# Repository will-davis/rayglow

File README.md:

# RayGLow

Audio-reactive GLSL visuals on a custom RGB LED wall. Music plays on a desktop; a small
daemon there reduces it to per-frame audio *features* and unicasts them over UDP to a
Raspberry Pi 5, which renders Shadertoy-dialect GLSL on its GPU, packs each frame, and
ships it over a **4-lane parallel bus** to an **RP2350b** microcontroller whose PIO+DMA
engine drives the HUB75 panels with zero-CPU, jitter-free timing. Write a shader, paste
it in, watch it move to the music.

https://github.com/user-attachments/assets/fb1bfaf4-e451-43c7-8cc3-830d7c186d91

```
desktop (optional)                 Raspberry Pi 5                         RP2350b PiZero + HAT
┌────────────────────────┐         ┌────────────────────────────┐         ┌───────────────────────┐
│ music ▶ sink monitor   │  UDP    │ feed.receiver (latest-win) │  4-lane │ phase6: PIO+DMA RX    │
│ sender.py: FFT ▶ bands │ ──────▶ │ render: GLSL ▶ pack        │   bus   │ zero-CPU scan-out     │
│ + flywheels/beat/key   │  :5005  │ (to_chains ▶ hub75.pack)   │ ──────▶ │ ▶ HUB75 ▶ 384×128 wall│
│ ▶ 2996-B v3 @ ~60 Hz   │ ~180KB/s│ headless EGL + GLES3       │ 192 KB  │ (2 chains × 12 panels)│
└────────────────────────┘         └────────────────────────────┘         └───────────────────────┘
        point $RAYGLOW_HOST ──────────────▶ your Pi
```

The three stages live in **one repo**. The desktop and Pi halves are Python: the desktop
runs `sender/`, the Pi runs the `rayglow` package installed editable (`pip install -e`)
from a copy of this repo — get it there however you like (`git pull`, or a continuous
file sync such as mutagen/sshfs for live shader editing). The RP2350b half is Rust
firmware (`firmware/`) flashed onto the board, plus a custom level-shifting HAT
(`hardware/`).
First-time setup is in [Deploy](#deploy); full credits and licensing are in
[ATTRIBUTION.md](ATTRIBUTION.md) (RayGLow is **MIT** — see [LICENSE](LICENSE)).

The desktop sender is **optional**: `rayglow.fake_sender` synthesizes the same packet
struct, so the Pi can drive the wall with no music source at all.

## Why features, not streamed audio

Streaming PCM means reconstructing a continuous signal on the far end: ring buffers,
clock-drift resampling, jitter buffers. Features are **stateless per frame** — a lost or
late packet just means the Pi renders with the previous values, and at 60 Hz one held
frame is invisible. The Pi does zero audio work, the wire carries ~0.25 MB/s, and UDP
gets used the way UDP wants to be used.

## Why offload scan-out to the RP2350b

Bit-banging HUB75 from a Linux SoC fights the scheduler — it needs a dedicated RT core
and still jitters (the Pi 5's RP1 southbridge made it worse). The RP2350b runs the refresh
loop entirely in **3 PIO state machines + 4 self-chaining DMA channels**, with the CPU
never touching the pixel path. The Pi renders at whatever rate it likes and ships 192 KB
frames over the link — already gamma-corrected on the Pi (the GPU resolve pass bakes
the firmware `lut.rs` CIE curve into each frame; `--readback legacy` instead applies
the packer's bit-exact LUT replica to a LINEAR readback); the RP2350b holds a
rock-steady, flicker-free refresh.

## Why a parallel bus, not SPI

The link was originally 1-lane SPI, and SPI still works as the proven fallback
(`--transport spi`). But a frame takes ~13 ms at 40 MHz SPI even at the v1 wall's 64 KB —
~39 ms at the v2 wall's 192 KB — long enough to sit squarely
on the critical path. A **4-lane source-synchronous parallel bus**, clocked out by the
Pi 5's RP1 PIO block, drops that to ~2 ms (clkdiv 3; ~1.3 ms at clkdiv 2). Only the wire
changes: the byte stream is identical to the SPI path (same `hub75.py` packer output,
same READY handshake), so the firmware and packer don't change. (4 lanes, not 8: the RP2350b scan-out engine owns
GP0–18, leaving GP19–27 for the link.) See
[`rayglow/render/piobridge/README.md`](rayglow/render/piobridge/README.md).

## Hardware

A **Waveshare RP2350-PiZero** on a custom HAT that level-shifts (3.3 V → 5 V via
`SN74AHCT245`) and breaks out two HUB75 chains + the Pi↔RP2350b link. Design files, the
KiCad project, and fab Gerbers are in [`hardware/`](hardware/).

## Repo layout

| path | what |
|---|---|
| `sender/` | **desktop half** — the feature daemon (`sender.py`), its own uv project (numpy + sounddevice). [sender/README.md](sender/README.md) has the protocol + feature detail. |
| `rayglow/feed/` | the audio-feature feed: packet `receiver`, `FeatureState`, and the rig `config` (geometry/network/gamma). Shared, dependency-free. |
| `rayglow/render/` | **the live renderer** — headless EGL + GLES3, multipass pipeline, iChannel textures (`audio`, `milk`, noise, images), hot reload, a TCP **control plane** (`control.py`: push/switch shaders + media controls), the GPU resolve pass + zero-copy dma-heap readback (`output.py`, `dmabuf.py`), the frame packer (`hub75.py`) + link backends (`spi_out.py`, `pio_out.py` / `piobridge/`), and `presets/*.glsl`. |
| `rayglow/fake_sender.py` | music-free test harness; emits the same packet struct with synthesized features. |
| `rayglow/link.py` | **remote render wire contract** — frame fragments out, flip credits back (UDP, latest-wins, credit-paced; see [REMOTE-RENDER-PLAN.md](REMOTE-RENDER-PLAN.md)). Shared by `render/net_out.py` (`--output net`) and `framesink`. |
| `rayglow/framesink.py` | the Pi when rendering happens elsewhere: reassemble frames → `drm_out` page flip → credit per vblank. A socket and a memcpy — no GL stack. |
| `rayglow.example.toml` | per-machine CLI defaults (`rayglow/userconf.py`): pin each machine's flags (`output`, `net-host`, `window`, …) in `~/.config/rayglow/config.toml` so production launches are just `python -m rayglow.render <shader>` / `python -m rayglow.framesink`. CLI flags always override. |
| `rayglow/spi_test.py` | static test pattern (no GL) — isolates the link/firmware/cabling from the renderer. Per-panel ID markers confirm the serpentine fold; runs over either transport. |
| `firmware/` | **RP2350b Rust firmware** — zero-CPU PIO+DMA HUB75 scan-out, brought up in verifiable phases. [firmware/README.md](firmware/README.md). |
| `hardware/` | **custom HAT** — KiCad project, Gerbers, and the locked net/pinout spec. [hardware/README.md](hardware/README.md). |
| `tools/` | `verify.py` — proves the Python packer (`render/hub75.py`) is byte-identical to the firmware via a Rust golden frame. `fold_check.py` — proves the serpentine fold + the geometry/SRAM contract from the desk. `link_check.py` — locks the remote-render frame link (fragments/credits/pacing) over loopback. `dmabuf_probe.py` — the readback benchmark. |
| `ROADMAP.md` | queued workstreams — the living handoff doc between working sessions. |
| `docs/design-history/` | the original project record (MilkDrop reverse-engineering, the RP2350 plan, the build-history brain-dump). Superseded by the docs above where they disagree. |

## Quickstart

**Desktop (sender, optional):**
```fish
cd sender
set -x RAYGLOW_HOST 192.168.0.50   # your Pi's IP (or pass --host); see LOCAL-SETUP.example.md
uv run sender.py                   # capture default sink's monitor -> the Pi
uv run sender.py --list-sources    # enumerate pulse sources
uv run sender.py --debug           # + raw pre-normalization band energies
```

**Pi (renderer)** — see [Deploy](#deploy) for first-time setup:
```fish
# headless, no root, no hardware: render -> animated GIF (works on a desktop GPU too)
python -m rayglow.render rayglow/render/presets/milk-verbose.glsl --dry-run 120 --no-listen

# on the Pi, driving the panels (root for GPIO):
sudo ~/venv/bin/python -m rayglow.render rayglow/render/presets/milk-verbose.glsl
```
`milk-verbose.glsl` is the live-feed reference card — every audio feature drawn as a
labeled bar. Run the sender on the desktop at the same time to see it react.

## Deploy

**Renderer (Raspberry Pi 5).** The Pi runs the same git checkout, installed editable into
a uv venv:

```fish
# on the Pi, first time:
git clone <your-fork-url> ~/rayglow
cd ~/rayglow
uv venv ~/venv
uv pip install --python ~/venv/bin/python -e '.[pi]'   # core + Pi link deps
# thereafter: update the checkout (git pull, or let your file sync — e.g. a
# mutagen session pushing from the dev machine — keep it current)
```

`.[pi]` pulls the Pi-only deps (`spidev`, `gpiozero`, `lgpio`); EGL/GLES come from system
libraries, not pip. Editable install (not `PYTHONPATH`) because `sudo` scrubs the
environment but respects the installed package; hardware mode keeps root for GPIO and to
re-read shader files on hot reload, so the clone must live somewhere root can read (e.g.
under `~`).

- **Parallel link (default, `--transport pio`):** build `piobridge/libpioshim.so`
  against the RP1 `piolib` first — see
  [`rayglow/render/piobridge/README.md`](rayglow/render/piobridge/README.md).
- **SPI fallback (`--transport spi`):** enable SPI and make sure
  `/sys/module/spidev/parameters/bufsiz >= 196608` so the v2 wall's 192 KB frame goes in
  one transfer (the default 4096 is far too small; size it to `hub75.FRAME_BYTES`).

Per-machine addresses/paths: see [`LOCAL-SETUP.example.md`](LOCAL-SETUP.example.md).

**Firmware (RP2350b).** Flash the board once: `phase6-parallel --features two-chain`
for the 4-lane bus (production) or `phase5-spi` for the SPI fallback. Toolchain
bootstrap and `cargo run`/`probe-rs` instructions are in
[`firmware/README.md`](firmware/README.md).

## Status

Working end-to-end: the desktop sender feeds the renderer, which packs frames the
firmware accepts byte-for-byte (`tools/verify.py` is green). The renderer hot-reloads
`.glsl` files live (edit, save, watch the panel recompile); for the fast dev loop a TCP
control plane (`tools/rayglow_ctl.py push`, or the `tools/nvim-rayglow.lua` save-hook)
ships edits straight to the running renderer in <100ms — skipping the file-sync lag —
and adds media controls (next/prev/play/pause/loop) plus live per-shader supersample
scale (`// rayglow: scale=N` directive or `rayglow-ctl scale`). The Phase 6 4-lane parallel
bus is the production transport (hardware-verified on the custom HAT driving the 256×64 v1
wall; the 384×128 v2 wall is in bring-up — host + firmware ship, cabling/SI pending, see
ROADMAP §5); the Phase 5 SPI link remains the proven fallback. A microphone input path
exists (`sender/esp32-mic/` + `sender/espnow-dongle/`). Next: pulling config into a
user-editable yaml so the project runs on someone else's wall/network by editing one
file.

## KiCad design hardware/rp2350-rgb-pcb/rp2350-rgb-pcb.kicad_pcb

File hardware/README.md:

# RayGLow hardware — RP2350-HUB75 HAT

The custom PCB that sits between the **Waveshare RP2350-PiZero** dev board and the
LED wall. It is deliberately minimal: it does **3.3 V → 5 V level-shifting** of all
HUB75 logic (via `SN74AHCT245` buffers), presents the **two HUB75 connectors**
(chains A & B = one 256×64 tile), breaks out the spare GPIO + power on J4 — which
now carries the Pi 5 ↔ RP2350 **4-lane parallel link** (DATA0–3/DCLK/READY, see
[`../rayglow/render/piobridge/README.md`](../rayglow/render/piobridge/README.md);
designed pre-fab as an SPI/sync breakout, same pins) — and carries a dedicated 5 V
rail for the buffers. It does **not**
power the panels (their 5 V goes straight to the panel lugs) and contains no MCU
support circuitry — the dev board owns crystal/flash/USB/core power.

See the repo-root [`README.md`](../README.md) for where this sits in the pipeline,
and [`../firmware/`](../firmware/) for the firmware that drives the panels through
this HAT.

## Doc map

| File | What |
|---|---|
| [`NET-SPEC.md`](NET-SPEC.md) | **The locked electrical spec** — component list, '245 mappings, HUB75 pinout, power/grounding rules. The input to schematic generation. Lock before editing the schematic. |
| [`POWER-AND-GROUNDING.md`](POWER-AND-GROUNDING.md) | **Bench-measured** power/ground findings (PicoScope): star-ground rules, ratiometric buffer-VCC, ground-bounce diagnosis, wire-gauge math, the 3-channel-PSU reality, HV-distribution v2. Refines NET-SPEC's buffer-rail note. |
| [`PIZERO-HEADER-PINOUT.md`](PIZERO-HEADER-PINOUT.md) | Physical header pin → **actual** RP2350 GPIO map, read off the board schematic. Critical: the Waveshare board is **not** standard Pi BCM (it transposes a few GPIO pairs). |
| [`NETLIST-REVIEW.md`](NETLIST-REVIEW.md) | QA notes on the generated netlist. |
| [`KICAD-AGENT-TOOLING.md`](KICAD-AGENT-TOOLING.md) | How the schematic was generated with SKiDL + which parts are human-in-the-loop (routing). |
| [`../docs/design-history/PROJECT-PLAN.md`](../docs/design-history/PROJECT-PLAN.md) | §6 (pin map) and §9 (HAT scope) — the original design intent. |

## Layout & fab

```
hardware/
├── NET-SPEC.md / PIZERO-HEADER-PINOUT.md / NETLIST-REVIEW.md   # design docs
├── POWER-AND-GROUNDING.md           # bench-measured power/ground findings
├── gen_hat.py / gen_hat_sklib.py    # SKiDL schematic generators (uv project)
├── pyproject.toml / uv.lock         # SKiDL + KiCad-symbol deps for the above
├── rp2350-hub75-hat.net             # generated netlist
├── rp2350-rgb-pcb/                  # the KiCad project (.kicad_pcb/.pro/.sch)
├── 3dprint/                         # enclosure STLs (base + cover)
└── fab/                             # plotted Gerbers + drill files (the fab deliverable)
```

The schematic is generated from `gen_hat.py` (run with `uv run gen_hat.py`); the
PCB layout (`rp2350-rgb-pcb/`) is hand-routed in KiCad. The `fab/` Gerbers are the
manufacturing output — send that folder (zipped) to a board house.

> Bench-gear note: the original plan's §14 instrumentation reality-check (e.g. the
> ≥100 MHz scope needed to validate 256-wide pixel-clock signal integrity) lives in
> [`../docs/design-history/PROJECT-PLAN.md`](../docs/design-history/PROJECT-PLAN.md).

## Wall v2 (in progress, ~80% assembled 2026-07-16)

This HAT drove the v1 256×64 wall (chains A & B, 4 panels each). The **v2 wall**
scales to **6 wide × 4 tall of P4-2121-64x32 tiles = 384×128 px** (1536×512 mm),
on a 2020 T-slot aluminium frame (2 horizontal + 4 vertical members) with
3D-printed panel connectors in [`3dprint/`](3dprint/) (`P4-*`, **WIP — not
committed until the PoC is built**; the tracked STLs there are the HAT enclosure).

**This same HAT and one RP2350b drive all 24 tiles** — no second board, no FPGA.
Each of the two HUB75 chains carries 12 panels serpentined across two panel rows
(J2 = the top half, J3 = the bottom half), which the Pi folds with
`render/hub75.to_chains`. The framebuffers land at 385 KB of the RP2350's 512 KB
SRAM (measured; 15 panels/chain is the ceiling), so the earlier "exceeds one
RP2350's envelope" concern was wrong — see [`../ROADMAP.md`](../ROADMAP.md) §5 for
the measurement and the refresh/brightness tradeoff. The open risk is **signal
integrity over a 12-deep chain** (only 4 was ever validated), settled on the bench.

Power moves to **2× 5 V/300 W/60 A** supplies split on the wall's horizontal
midline — the same boundary as the chain A/B split, so each rail's return current
stays inside its own chain's domain. See
[`POWER-AND-GROUNDING.md`](POWER-AND-GROUNDING.md) (§ "Wall v2").

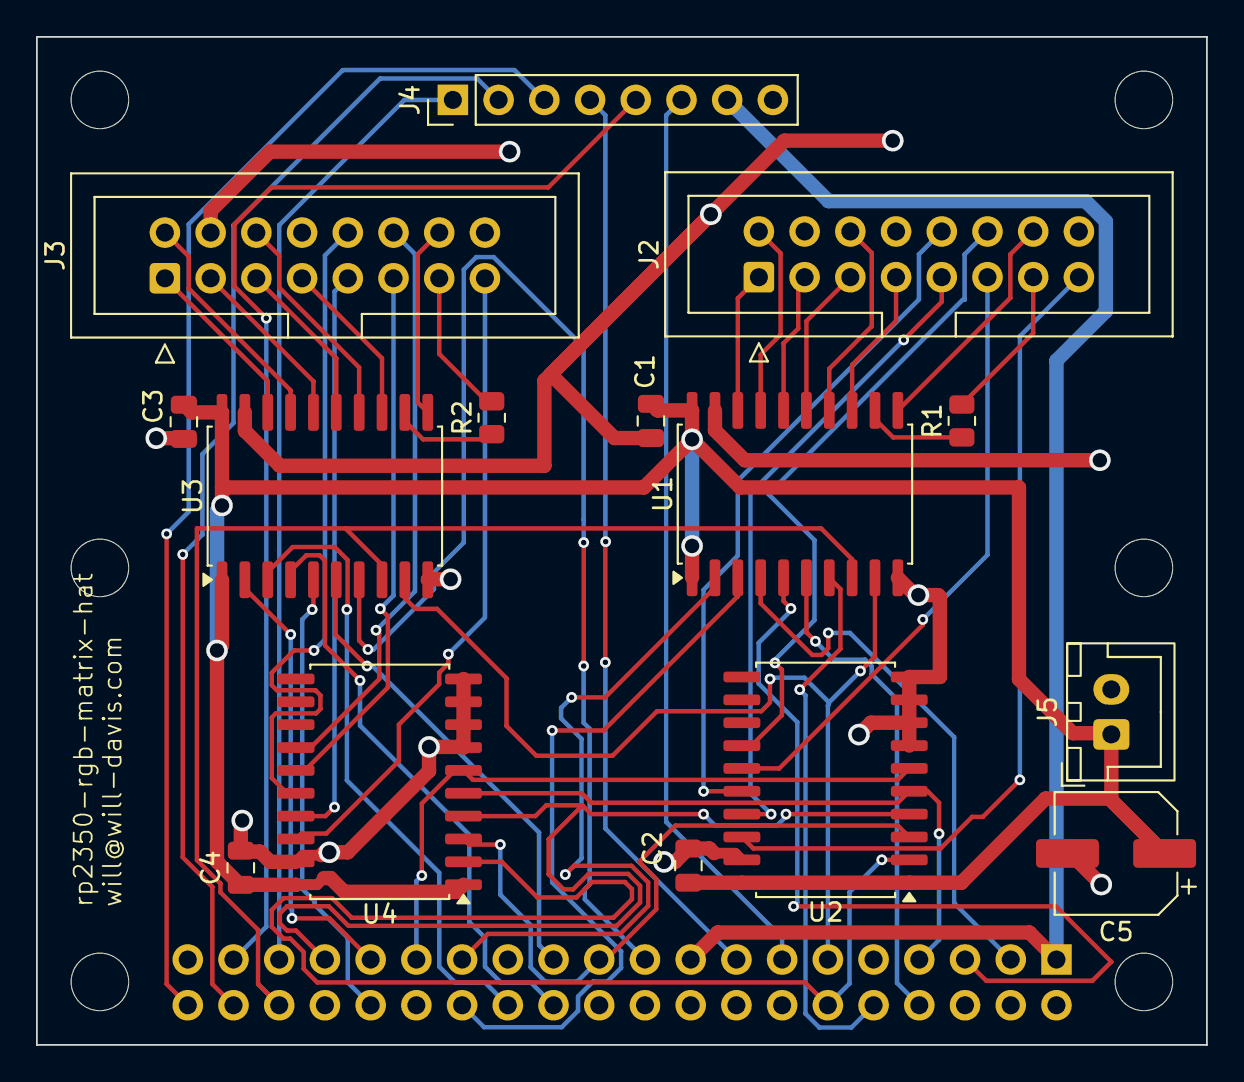
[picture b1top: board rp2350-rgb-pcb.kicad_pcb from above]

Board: 2 copper layers, 65.0 x 56.0 mm, 16 parts (1 on the bottom side), 56 nets.

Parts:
C1, C2, C3, C4: 100nF; C_0805_2012Metric
C5: 100uF; CP_Elec_6.3x7.7
J1: RP2350-PiZero; PinSocket_2x20_P2.54mm_Vertical
J2: HUB75_A; IDC-Header_2x08_P2.54mm_Vertical
J3: HUB75_B; IDC-Header_2x08_P2.54mm_Vertical
J4: SPI_SYNC; PinHeader_1x08_P2.54mm_Vertical
J5: +5V_IN; JST_XH_B2B-XH-A_1x02_P2.50mm_Vertical
R1, R2: 22; R_0805_2012Metric
U1, U2, U3, U4: SN74AHCT245DWR; SOIC-20W_7.5x12.8mm_P1.27mm

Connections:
+3V3: J1.1, J1.17, J4.7
+5V: C1.1, C2.1, C3.1, C4.1, C5.1, J5.1, U1.1, U1.20, U2.1, U2.20, U3.1, U3.20, U4.1, U4.20
GND: C1.2, C2.2, C3.2, C4.2, C5.2, J1.6, J1.9, J1.14, J1.20, J1.25, J1.30, J1.34, J1.39, J2.4, J2.8, J2.16, J3.4, J3.8, J3.16, J4.8, J5.2, U1.10, U1.19, U2.7, U2.8, U2.9, U2.10, U2.19, U3.10, U3.19, U4.7, U4.8, U4.9, U4.10, U4.19
GP0: J1.27, U1.2
GP1: J1.28, U1.3
GP2: J1.3, U1.4
GP3: J1.5, U1.5
GP4: J1.8, U1.6
GP5: J1.10, U1.7
GP6: J1.31, U3.2
GP7: J1.26, U3.3
GP8: J1.24, U3.4
GP9: J1.32, U3.5
GP10: J1.23, U3.6
GP11: J1.19, U3.7
GP12: J1.21, U2.3, U4.3
GP13: J1.33, U2.4, U4.4
GP14: J1.7, U2.5, U4.5
GP15: J1.29, U2.6, U4.6
GP16: J1.36, U1.8, U3.8
GP17: J1.11, U1.9, U3.9
GP18: J1.12, U2.2, U4.2
GP19: J1.35, J4.1
GP20: J1.38, J4.2
GP21: J1.40, J4.3
GP22: J1.15, J4.4
GP26: J1.37, J4.5
GP27: J1.13, J4.6
unnamed: J2.1, U1.18
unnamed: J2.2, U1.17
unnamed: J2.3, U1.16
unnamed: J2.5, U1.15
unnamed: J2.6, U1.14
unnamed: J2.7, U1.13
unnamed: R1.1, U1.12
unnamed: J2.13, R1.2
unnamed: J2.14, U1.11
unnamed: J2.15, U2.18
unnamed: J2.9, U2.17
unnamed: J2.10, U2.16
unnamed: J2.11, U2.15
unnamed: J2.12, U2.14
unnamed: J3.1, U3.18
unnamed: J3.2, U3.17
unnamed: J3.3, U3.16
unnamed: J3.5, U3.15
unnamed: J3.6, U3.14
unnamed: J3.7, U3.13
unnamed: R2.1, U3.12
unnamed: J3.13, R2.2
unnamed: J3.14, U3.11
unnamed: J3.15, U4.18
unnamed: J3.9, U4.17
unnamed: J3.10, U4.16
unnamed: J3.11, U4.15
unnamed: J3.12, U4.14

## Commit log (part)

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2026-06-14 Updated for rp2350 SPI communication output. 64kb frames for injestion. -will
2026-06-15 Add link to GitHub assets in README
    Added a link to the GitHub assets in the README.
2026-06-15 Fix formatting issues in README.md
2026-06-15 Major overhaul. Folding in rp2350 firmware and trimming legacy files.
2026-06-15 Fix formatting in README diagram
    Correct formatting and spacing in the diagram.
2026-06-17 added some experimental features. staging v2
2026-06-17 modifying gitignore
2026-06-17 modified config to match rpi
2026-06-17 Vectorize bit-plane pack + async PBO readback
2026-06-18 Added 4 lane parallel bus using PIO
2026-06-18 removed redundant link
2026-06-18 modified gitignore
2026-06-18 untrack and ignore root-level will-notes.md
2026-06-18 updated README.md - the old one was a mess
